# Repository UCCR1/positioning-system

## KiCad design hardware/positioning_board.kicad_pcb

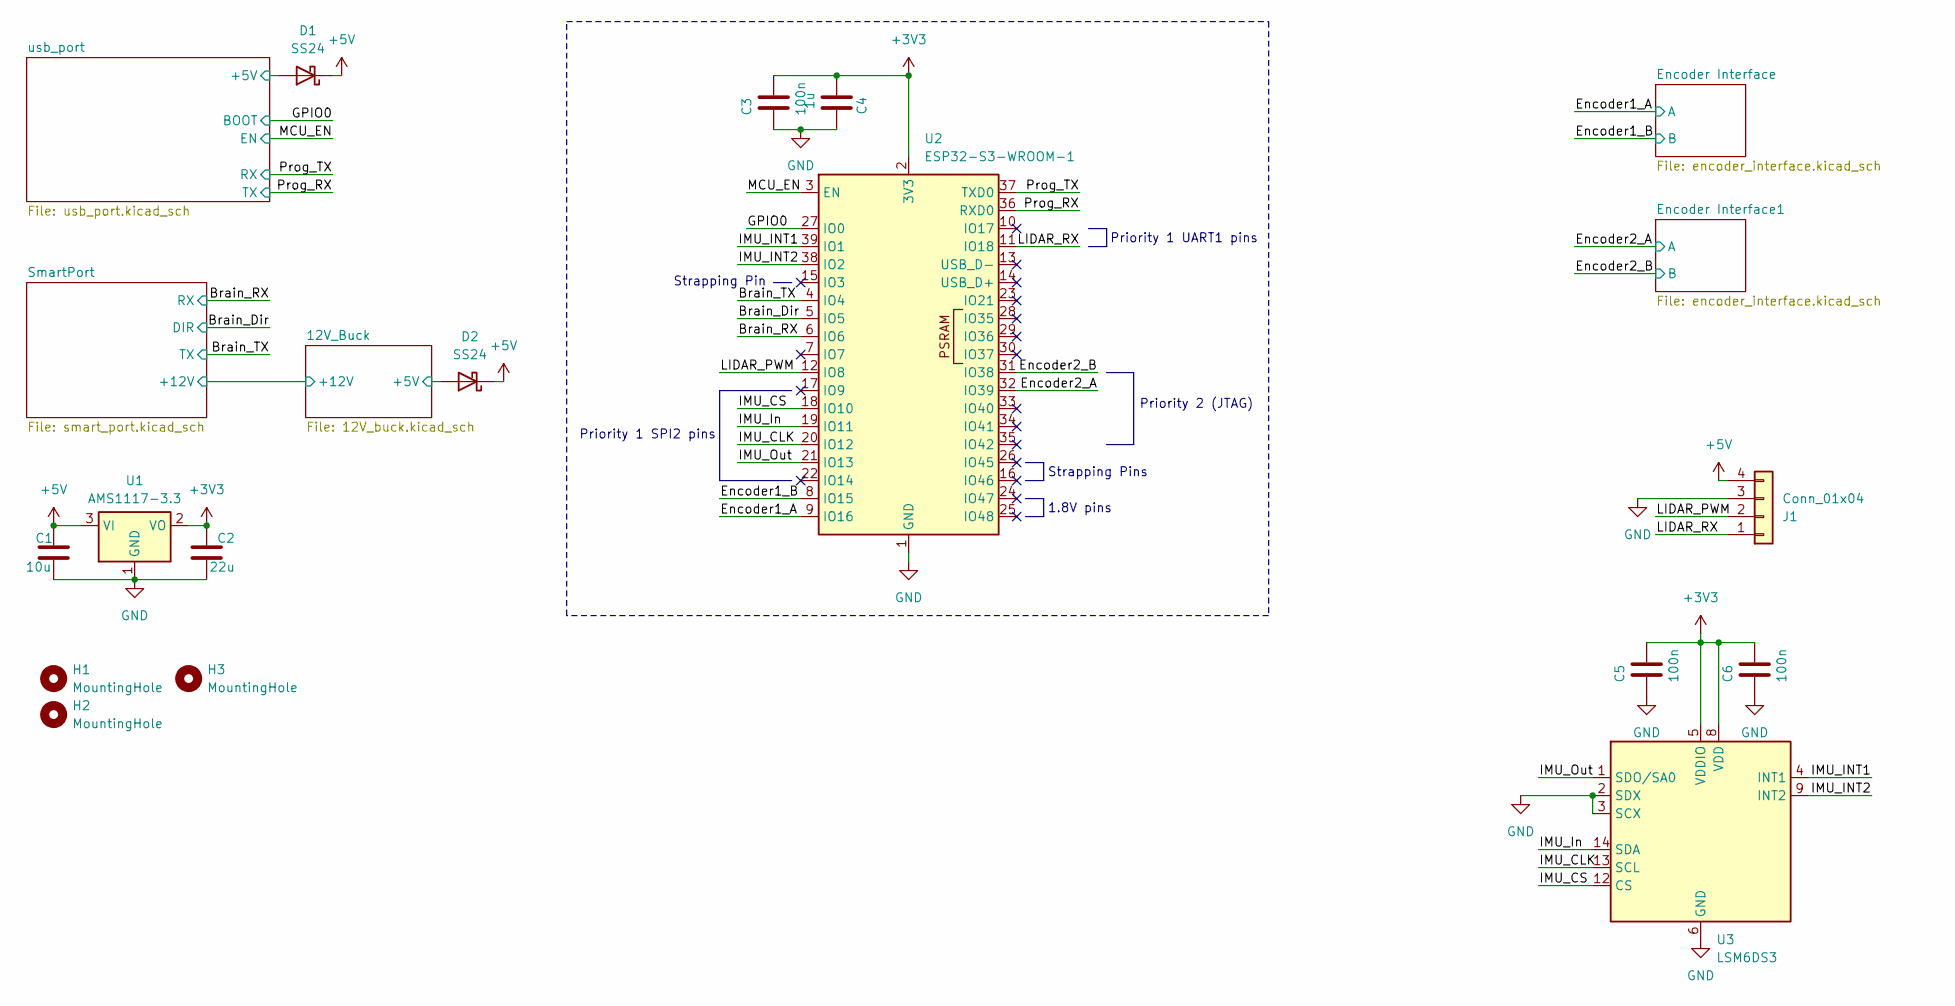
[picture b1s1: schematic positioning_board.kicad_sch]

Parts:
C1: 10u; C_0603_1608Metric
C2: 22u; C_0603_1608Metric
C3, C5, C6: 100n; C_0603_1608Metric
C4: 1u; C_0603_1608Metric
D1, D2: SS24; D_SMA; LCSC C2891713
H1, H2, H3: MountingHole; MountingHole_4.3mm_M4
J1: Conn_01x04; JST_ZH_B4B-ZR_1x04_P1.50mm_Vertical; LCSC C157997
U1: AMS1117-3.3; SOT-223-3_TabPin2; LCSC C6186
U2: ESP32-S3-WROOM-1; ESP32-S3-WROOM-1U; LCSC C3013946
U3: LSM6DS3; LGA-14_3x2.5mm_P0.5mm_LayoutBorder3x4y

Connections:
+3V3: C2.2, C3.2, C4.1, C5.2, C6.2, U1.2 (VO), U2.2 (3V3), U3.5 (VDDIO), U3.8 (VDD); also elsewhere on the board
+5V: C1.2, D1.1 (K), D2.1 (K), J1.4, U1.3 (VI); also elsewhere on the board
/12V_Buck/+5V: D2.2 (A); also elsewhere on the board
/Brain_Dir: U2.5 (IO5); also elsewhere on the board
/Brain_RX: U2.6 (IO6); also elsewhere on the board
/Brain_TX: U2.4 (IO4); also elsewhere on the board
/Encoder1_A: U2.9 (IO16); also elsewhere on the board
/Encoder1_B: U2.8 (IO15); also elsewhere on the board
/Encoder2_A: U2.32 (IO39); also elsewhere on the board
/Encoder2_B: U2.31 (IO38); also elsewhere on the board
/GPIO0: U2.27 (IO0); also elsewhere on the board
/IMU_CLK: U2.20 (IO12), U3.13 (SCL)
/IMU_CS: U2.18 (IO10), U3.12 (CS)
/IMU_INT1: U2.39 (IO1), U3.4 (INT1)
/IMU_INT2: U2.38 (IO2), U3.9 (INT2)
/IMU_In: U2.19 (IO11), U3.14 (SDA)
/IMU_Out: U2.21 (IO13), U3.1 (SDO/SA0)
/LIDAR_PWM: J1.2, U2.12 (IO8)
/LIDAR_RX: J1.1, U2.11 (IO18)
/MCU_EN: U2.3 (EN); also elsewhere on the board
/Prog_RX: U2.36 (RXD0); also elsewhere on the board
/Prog_TX: U2.37 (TXD0); also elsewhere on the board
/usb_port/+5V: D1.2 (A); also elsewhere on the board
GND: C1.1, C2.1, C3.1, C4.2, C5.1, C6.1, J1.3, U1.1 (GND), U2.1 (GND), U2.40 (GND), U2.41 (GND), U3.2 (SDX), U3.3 (SCX), U3.6 (GND), U3.7 (GND); also elsewhere on the board

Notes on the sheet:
Priority 2 (JTAG)
Strapping Pins
Strapping Pin
Priority 1 UART1 pins
1.8V pins
Priority 1 SPI2 pins

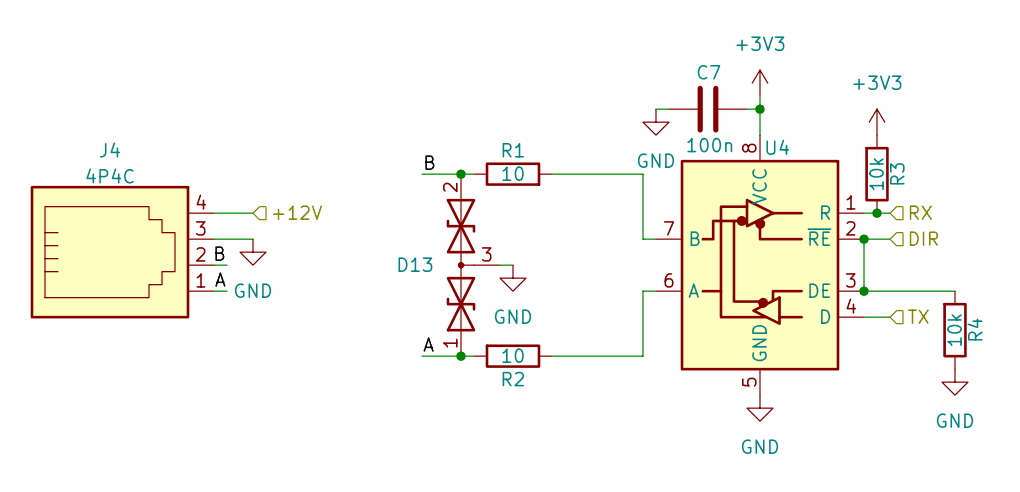
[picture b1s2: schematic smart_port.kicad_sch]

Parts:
C7: 100n; C_0603_1608Metric
D13: CESD3V3AP; SOT-23
J4: 4P4C; RJ11-4P4C; LCSC C189737
R1, R2: 10; R_0603_1608Metric
R3, R4: 10k; R_0603_1608Metric
U4: SN65HVD1782DR; SOIC-8_3.9x4.9mm_P1.27mm; LCSC C183092

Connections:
+3V3: C7.1, R3.2, U4.8 (VCC); also elsewhere on the board
/12V_Buck/+12V: J4.4; also elsewhere on the board
/Brain_Dir: R4.2, U4.2 (~RE), U4.3 (DE); also elsewhere on the board
/Brain_RX: R3.1, U4.1 (R); also elsewhere on the board
/Brain_TX: U4.4 (D); also elsewhere on the board
/SmartPort/A: D13.1 (A1), J4.1, R2.2
/SmartPort/B: D13.2 (A2), J4.2, R1.1
GND: C7.2, D13.3 (common), J4.3, R4.1, U4.5 (GND); also elsewhere on the board
unnamed: R2.1, U4.6 (A)
unnamed: R1.2, U4.7 (B)

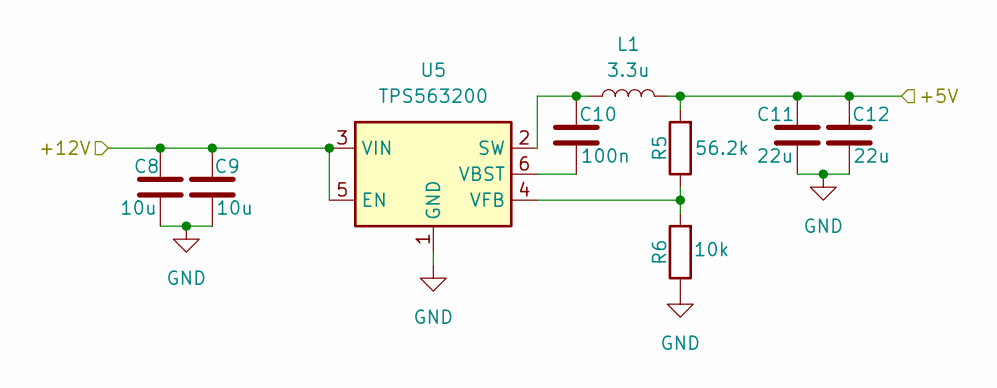
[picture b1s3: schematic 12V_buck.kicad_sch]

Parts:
C8, C9: 10u; C_0603_1608Metric
C10: 100n; C_0603_1608Metric
C11, C12: 22u; C_0603_1608Metric
L1: 3.3u; L_Changjiang_FXL0630; LCSC C167219
R5: 56.2k; R_0603_1608Metric
R6: 10k; R_0603_1608Metric
U5: TPS563200; SOT-23-6

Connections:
/12V_Buck/+5V: C11.2, C12.2, L1.2, R5.2; also elsewhere on the board
/12V_Buck/+12V: C8.2, C9.2, U5.3 (VIN), U5.5 (EN); also elsewhere on the board
GND: C8.1, C9.1, C11.1, C12.1, R6.1, U5.1 (GND); also elsewhere on the board
unnamed: C10.2, L1.1, U5.2 (SW)
unnamed: C10.1, U5.6 (VBST)
unnamed: R5.1, R6.2, U5.4 (VFB)

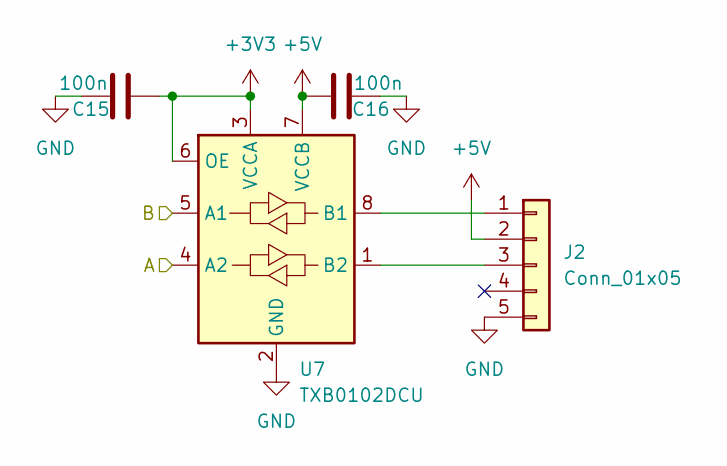
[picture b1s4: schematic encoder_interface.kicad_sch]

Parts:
C15, C16: 100n; C_0603_1608Metric
J2: Conn_01x05; JST_XH_S5B-XH-A_1x05_P2.50mm_Horizontal
U7: TXB0102DCU; VSSOP-8_2.3x2mm_P0.5mm

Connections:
+3V3: C15.1, U7.3 (VCCA), U7.6 (OE); also elsewhere on the board
+5V: C16.1, J2.2, U7.7 (VCCB); also elsewhere on the board
/Encoder1_A: U7.4 (A2); also elsewhere on the board
/Encoder1_B: U7.5 (A1); also elsewhere on the board
GND: C15.2, C16.2, J2.5, U7.2 (GND); also elsewhere on the board
unnamed: J2.1, U7.8 (B1)
unnamed: J2.3, U7.1 (B2)

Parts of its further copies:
C17, C18: 100n; C_0603_1608Metric
J3: Conn_01x05; JST_XH_S5B-XH-A_1x05_P2.50mm_Horizontal
U8: TXB0102DCU; VSSOP-8_2.3x2mm_P0.5mm

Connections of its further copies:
+3V3: C17.1, U8.3 (VCCA), U8.6 (OE); also elsewhere on the board
+5V: C18.1, J3.2, U8.7 (VCCB); also elsewhere on the board
/Encoder2_A: U8.4 (A2); also elsewhere on the board
/Encoder2_B: U8.5 (A1); also elsewhere on the board
GND: C17.2, C18.2, J3.5, U8.2 (GND); also elsewhere on the board
unnamed: J3.1, U8.8 (B1)
unnamed: J3.3, U8.1 (B2)

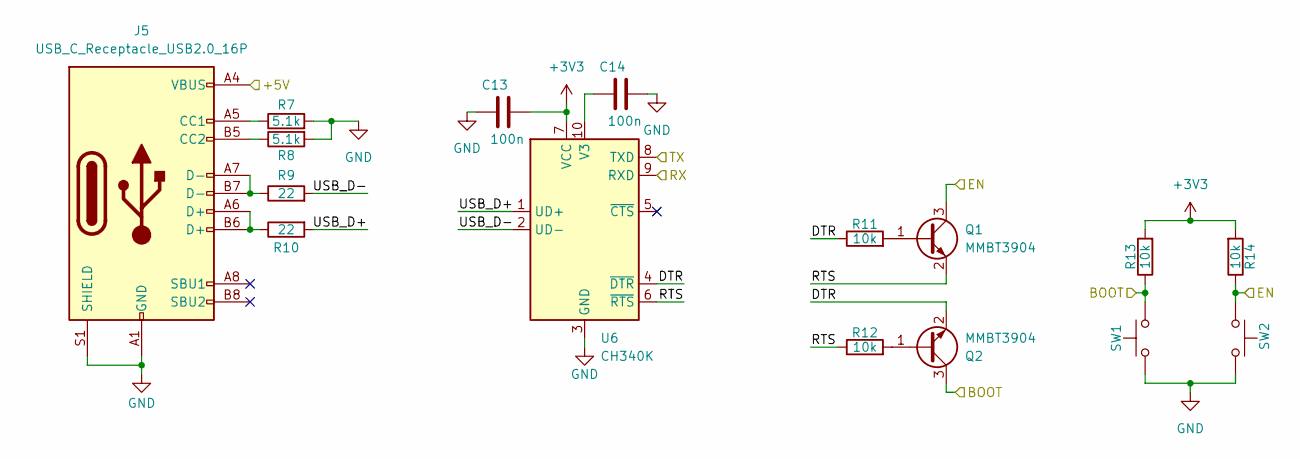
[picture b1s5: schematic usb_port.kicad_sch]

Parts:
C13, C14: 100n; C_0603_1608Metric
J5: USB_C_Receptacle_USB2.0_16P; USB_C_Receptacle_GCT_USB4105-xx-A_16P_TopMnt_Horizontal; LCSC C2927038
Q1, Q2: MMBT3904; SOT-23; LCSC C20526
R7, R8: 5.1k; R_0603_1608Metric
R9, R10: 22; R_0603_1608Metric
R11, R12, R13, R14: 10k; R_0603_1608Metric
SW1, SW2: SW_Push; SW_SPST_TS-1088-xR020; LCSC C720477
U6: CH340K; SSOP-10-1EP_3.9x4.9mm_P1mm_EP2.1x3.3mm; LCSC C968586

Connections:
+3V3: C13.2, R13.2, R14.2, U6.7 (VCC); also elsewhere on the board
/GPIO0: Q2.3 (C), R13.1, SW1.2; also elsewhere on the board
/MCU_EN: Q1.3 (C), R14.1, SW2.2; also elsewhere on the board
/Prog_RX: U6.8 (TXD); also elsewhere on the board
/Prog_TX: U6.9 (RXD); also elsewhere on the board
/usb_port/+5V: J5.A4 (VBUS), J5.A9 (VBUS), J5.B4 (VBUS), J5.B9 (VBUS); also elsewhere on the board
/usb_port/DTR: Q2.2 (E), R11.1, U6.4 (~DTR)
/usb_port/RTS: Q1.2 (E), R12.1, U6.6 (~RTS)
/usb_port/USB_D+: R10.2, U6.1 (UD+)
/usb_port/USB_D-: R9.2, U6.2 (UD-)
GND: C13.1, C14.2, J5.A1 (GND), J5.A12 (GND), J5.B1 (GND), J5.B12 (GND), J5.S1 (SHIELD), R7.2, R8.2, SW1.1, SW2.1, U6.3 (GND), U6.11 (GND); also elsewhere on the board
unnamed: J5.A5 (CC1), R7.1
unnamed: J5.B5 (CC2), R8.1
unnamed: J5.A6 (D+), J5.B6 (D+), R10.1
unnamed: J5.A7 (D-), J5.B7 (D-), R9.1
unnamed: Q1.1 (B), R11.2
unnamed: Q2.1 (B), R12.2
unnamed: C14.1, U6.10 (V3)

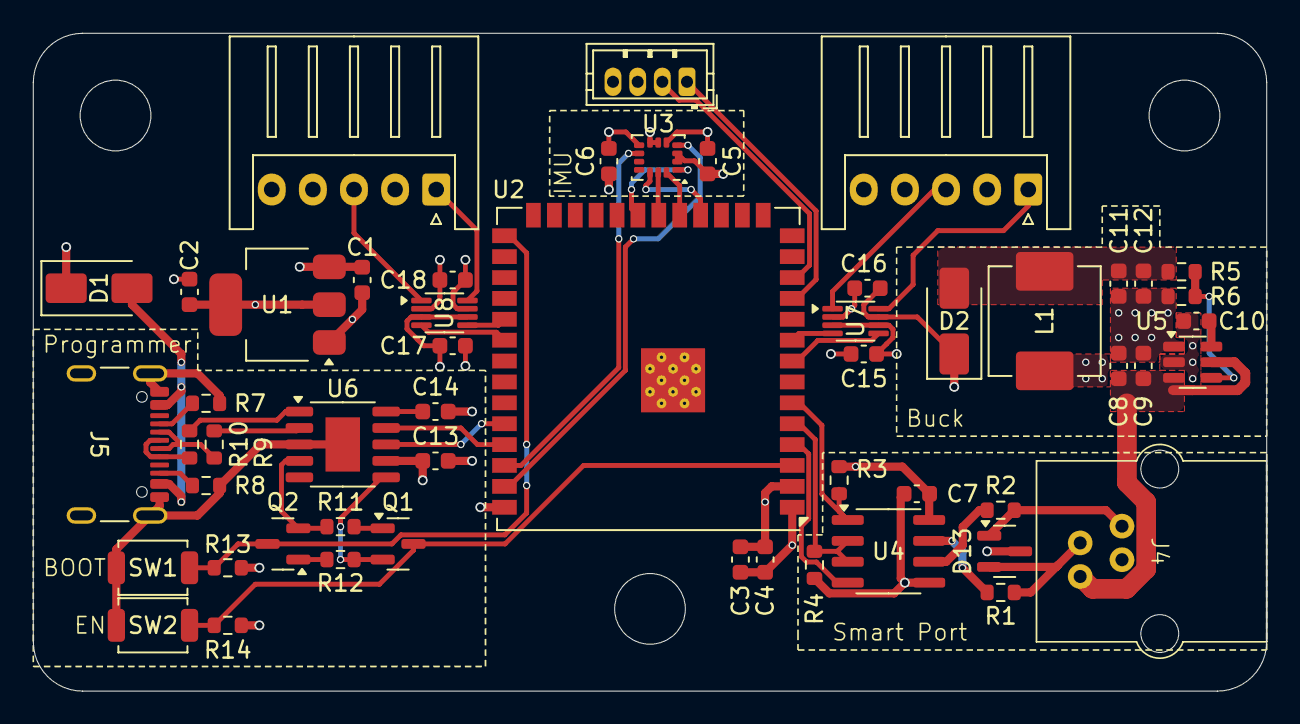
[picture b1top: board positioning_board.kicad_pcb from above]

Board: 4 copper layers, 75.0 x 40.0 mm, 56 parts (0 on the bottom side), 47 nets.

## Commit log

2026-02-11 add initial hardware
2026-02-11 init cargo workspace
2026-02-11 init esp project
2026-02-11 add no_std
2026-02-11 Added line seg, vector, and started fieldmap implementation
2026-02-11 Added something something fieldmap
2026-02-11 explicit iterator thingy
2026-02-11 actually compile
2026-02-13 Created positioning-lib library
2026-02-23 feat: draft layout
2026-02-23 reroute lidar pins
2026-02-23 reroute some pins
2026-02-24 refactor into sub sheets
2026-02-24 relayout board
2026-02-24 swap lidar and brain UART channels
2026-02-24 switch to 4 layer
2026-02-24 optimize size
2026-02-24 fix programmer differential routing
2026-02-24 add empty space around holes
2026-02-24 fix: remove traces from underneath IMU
2026-02-24 add back labels
2026-02-25 add logic level shifters
2026-03-02 basic odom
2026-03-03 generic N wheel odom
2026-03-04 encoder counter barebones
2026-03-04 initial multi encoder impl
2026-03-04 refactor: switch back to atomics
2026-03-11 more vector stuff
2026-03-11 refactor vector things
2026-03-12 feat: linear algebra N wheel solution
2026-03-12 feat: generic matrix math
2026-03-12 feat: lidar packet parser
2026-03-12 feat: encoder angle position import odom into firmware
2026-03-12 feat: macro encoder definition
2026-03-12 feat: impl odometry task
2026-03-12 import formatting
2026-03-12 feat: uart lidar parsing
2026-03-12 refactor: extract continuous bytes reader
2026-03-12 refactor: bring linalg into own crate
2026-03-12 reduce encoder macro size
2026-03-13 feat: Matrix solver
2026-03-13 remove uneccessary tuple layer
2026-03-13 refactor: use num_traits zero+one
2026-03-13 feat: simplified 2D line intersection
2026-03-13 refactor: move field stuff to position lib
2026-03-13 Added generic sensor trait
2026-03-13 feat: libm uom
2026-03-13 const unit vectors
2026-03-13 fix: float roots
2026-03-13 feat: imu register behavior
2026-03-14 feat: Imu task
2026-03-14 fix: encoders not wrapping negative
2026-03-15 feat: circle intersection
2026-03-18 I dunno forgot to push last time
2026-04-03 initial imu integration
2026-04-03 fix: faulty filler packet parsing
2026-04-03 refactor: extract imu logic to own crate
2026-04-04 feat: test circuit code
2026-04-04 feat: quaternions
2026-04-04 feat: calibration
2026-04-04 fix: incorerct quaternion euler conversion
2026-04-04 feat: interrupt based gyro polling
2026-04-04 feat: generic calibration struct
2026-04-04 fix: proper sensitivity for both imu modules
2026-04-13 refactor: seperate angular velocity and linear acceleration traits
2026-04-13 refactor: extract angular position integration to imu-lib
2026-04-13 rename base to inner
2026-04-13 refactor: consolidate calibration and integration
2026-04-13 refactor: rename modules to devices
2026-04-13 feat: linear position/velocity integration
2026-04-23 start montecarlo positioning
